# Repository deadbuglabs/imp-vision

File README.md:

# imp-vision

IMP-VISION — Deadbug Labs AI smart glasses: real thermal imaging + night vision, phone-linked. Temple board, firmware, and app.

The glasses connect to a phone and nothing else — no hub, no cloud account, no builder-supplied parts. Complete glasses in the box; the phone app is where the AI experience lives.

## What it sees

Real thermal imaging and real night vision, fused, in glasses you would wear anywhere. Nobody sells that combination. Fused thermal + night-vision systems exist only as military gear — helmet-mounted, bulky, issued rather than bought. IMP-VISION is being built to put both senses in an ordinary frame.

- **Thermal imaging** — a FLIR Lepton-class 160×120 radiometric core on the full-sense build. Real heat signatures, not blobs.
- **Night vision** — a no-IR-cut camera with 940 nm illuminators that emit no visible glow.
- **IR Source Watch** — passive detection of other active IR emitters (camera night-vision arrays, illuminators), labelled with classification and confidence.
- **Camera + microphone** — with a recording LED that is hardwired to the camera: no firmware path can light the camera without lighting the LED.

## Your models, your pick

The app takes any compatible Hugging Face model per role — Eyes, Brain, Ears, Voice — GGUF with mmproj for vision, sized to your phone, license shown before download. Defaults are preselected; the picker is open. Model sets: [Devilishcode/imp-vision-model-sets](https://huggingface.co/Devilishcode/imp-vision-model-sets)

## Status — 2026-11-21

- Temple board (ESP32-S3): routing at 50 unconnected nets, 0 shorts. Not DRC-clean, not fab-ready; a placement respin is the next step.
- Temple firmware v0: compiles clean. The firmware is a dumb pipe — the phone does the thinking.
- Phone app: v0.10.3 — glasses link layer, IR Watch, and a thermal preview surface all working against the phone camera.
- Display variants: in evaluation. The base build is audio-first, no display.

## Design documents

- [app-design.md](app-design.md) — the companion app: voice-first UI, senses, model picker
- [INTEGRATION.md](INTEGRATION.md) — how the temple board, frames, and sensors fit together
- [RING_DESIGN.md](RING_DESIGN.md) — the BLE scroll + click ring
- [INPUT_SOURCES.md](INPUT_SOURCES.md) — ring, mouse, and other input classes
- [PAIR_IMP_PROTOCOL.md](PAIR_IMP_PROTOCOL.md) — how the glasses pair with an IMP-1, and the hard limits on what they may ask it to do
- [SCREEN_CONTROL.md](SCREEN_CONTROL.md) — the display control model for display variants

Deadbug Labs — boards and devices for people who build. https://deadbuglabs.github.io/

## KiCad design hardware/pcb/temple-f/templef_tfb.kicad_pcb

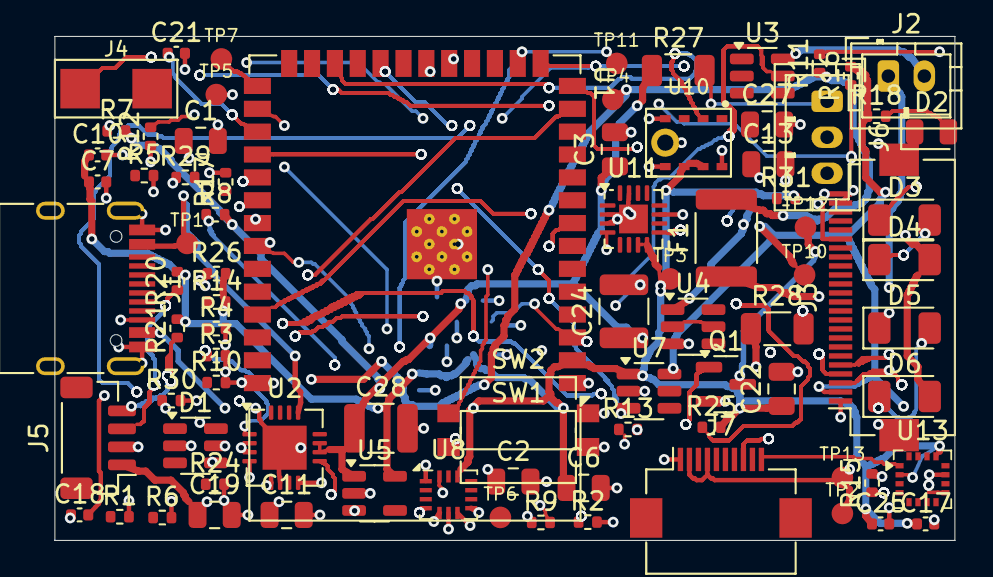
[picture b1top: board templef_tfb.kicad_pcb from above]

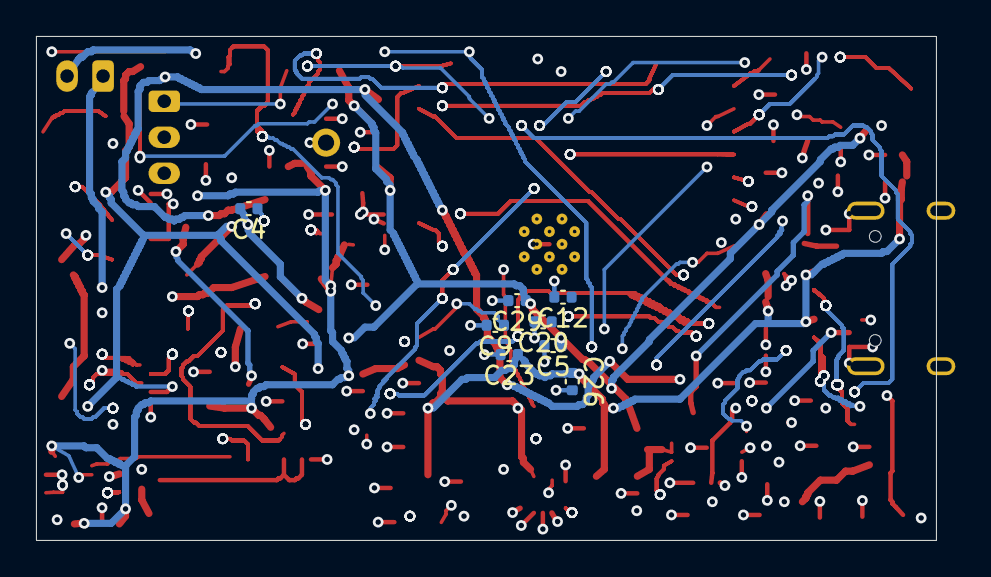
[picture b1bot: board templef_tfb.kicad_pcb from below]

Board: 4 copper layers, 50.0 x 28.0 mm, 91 parts (8 on the bottom side), 70 nets.

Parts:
C1, C2, C3, C6, C11, C13, C19, C22, C27: C_0805_2012Metric
C4, C5, C7, C9, C10, C12, C17, C18, C20, C21, C23, C25, C26, C29: C_0402_1005Metric
C24, C28: C_1210_3225Metric
D1: SOT-23-6
D2: LED_0805_2012Metric
D3, D4, D5, D6: VSMY12940; LED_1206_3216Metric
F1: Fuse_1812_4532Metric
J1: USB_C_Receptacle_HRO_TYPE-C-31-M-12
J2: JST_PH_B2B-PH-K_1x02_P2.00mm_Vertical
J3: Hirose_FH12-24S-0.5SH_1x24-1MP_P0.50mm_Horizontal
J4: J4_Transducer_Lands_2P_P4.0mm
J5: JST_SH_BM04B-SRSS-TB_1x04-1MP_P1.00mm_Vertical
J6: JST_PH_B3B-PH-K_1x03_P2.00mm_Vertical
J7: Hirose_FH12-10S-0.5SH_1x10-1MP_P0.50mm_Horizontal
Q1: SOT-23
R1, R2, R3, R4, R5, R6, R7, R8, R9, R10, R11, R12, R13, R14, R15, R16, R17, R18, R20, R21, R24, R25, R26, R29, R30, R31: R_0402_1005Metric
R27, R28: R_1206_3216Metric
SW1, SW2: SW_Tactile_SPST_NO_Straight_CK_PTS636Sx25SMTRLFS
TP1, TP2, TP3, TP4, TP5, TP6, TP7, TP10, TP11, TP12, TP13: TP_Pad_D1.2mm
U1: ESP32-S3-WROOM-1
U2: QFN-16-1EP_4x4mm_P0.5mm_EP2.45x2.45mm
U3, U4, U7: SOT-23-6
U5: SOT-23-5
U8: Bosch_LGA-14_3x2.5mm_P0.5mm
U10: INMP441_LGA_4.72x3.76
U11: TQFN-16-1EP_3x3mm_P0.5mm_EP1.6x1.6mm
U13: LGA-16_3x3mm_P0.5mm

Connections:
AMP_SD: U1.22, U11.4
BATT_ADC: R11.2, R12.2, U1.15
BAT_CELL: C2.1, F1.2, R9.1, R11.1, TP4.1, U2.2, U2.3
BOOT: R14.1, TP7.1, U1.27
BTN_PHOTO: C21.1, R26.1, SW2.1, U1.29
BTN_PTT: C20.1, R25.1, SW1.1, U1.28
CAM_3V3: C13.1, J3.2, J3.20, R15.2, R16.2, R18.1, TP10.1, U7.6
CAM_CT: C12.1, U7.5
CAM_D0: J3.16, U1.39
CAM_D1: J3.15, U1.38
CAM_D2: J3.14, U1.4
CAM_D3: J3.13, U1.5
CAM_D4: J3.12, U1.6
CAM_D5: J3.11, U1.7
CAM_D6: J3.10, U1.12
CAM_D7: J3.9, U1.17
CAM_HREF: J3.6, U1.9
CAM_PCLK: J3.7, U1.21
CAM_PWDN: J3.18, R17.1
CAM_PWR_EN: U1.30, U7.3
CAM_RESET: J3.17, U1.10
CAM_SIOC: J3.3, R15.1, U1.20
CAM_SIOD: J3.4, R16.1, U1.19
CAM_VSYNC: J3.5, U1.8
CAM_XCLK: J3.8, U1.18
CC1: J1.A5, R1.1
CC2: J1.B5, R2.1
CELL_NEG: C4.2, J2.2, U3.6, U4.1
CELL_POS: F1.1, J2.1
CHG_ILIM: R4.1, U2.12
CHG_ISET: R5.1, U2.16
CHG_PGOOD: R7.1, U1.33, U2.7
CHG_STAT: R8.1, U1.32, U2.9
CHG_TMR: R6.1, U2.14
CHG_TS: R3.1, U2.1
EN: C9.1, R13.1, TP6.1, U1.3
GND: C1.2, C2.2, C3.2, C5.2, C6.2, C7.2, C9.2, C10.2, C11.2, C12.2, C13.2, C17.2, C18.2, C19.2, C20.2, C21.2, C22.2, C23.2, C24.2, C25.2, C26.2, C27.2, C28.2, C29.2, D1.2, D2.1, J1.A1, J1.A12, J1.B1, J1.B12, J1.S1, J3.1, J3.19, J3.23, J3.24, J3.MP, J5.2, J7.1, Q1.2, R1.2, R2.2, R3.2, R4.2, R5.2, R6.2, R10.2, R12.1, R17.2, R24.2, R30.2, SW1.2, SW2.2, TP5.1, U1.1, U1.40, U1.41, U2.4, U2.6, U2.8, U2.17, U4.3, U5.2, U7.2, U8.1, U8.6, U8.7, U10.4, U10.5, U10.6, U10.9, U11.2, U11.3, U11.11, U11.15, U11.17, U13.9, U13.11
I2C_SCL: J5.4, J7.10, R21.1, U1.35, U8.13, U13.1
I2C_SDA: J5.3, J7.9, R20.1, U1.34, U8.14, U13.16
I2S_BCLK: U1.11, U10.1, U11.16
I2S_DIN: R24.1, U1.24, U10.2
I2S_DOUT: U1.25, U11.1
I2S_WS: U1.23, U10.3, U11.14
ILL_A1: D3.1, J6.1, R27.2
ILL_A2: D5.1, J6.2, R28.2
ILL_G: Q1.1, R29.2, R30.1
ILL_K: D4.2, D6.2, J6.3, Q1.3, TP12.1
ILL_M1: D3.2, D4.1
ILL_M2: D5.2, D6.1
IMU_INT: TP11.1, U1.16, U8.4
IR_ILLUM_EN: R29.1, U1.31
LEP_CS: J7.8, R31.1, U1.37
LEP_MISO: J7.6, U1.26
LEP_SCK: J7.7, U1.36
MAG_CAP: C27.1, U13.10
PROT_CS: R10.1, U3.2
PROT_DMID: U4.2, U4.5
PROT_OC: U3.3, U4.4
PROT_OD: U3.1, U4.6
PROT_VDD_F: C4.1, R9.2, U3.5
REC_LED_A: D2.2, R18.2
SPK_N: J4.2, U11.10
SPK_P: J4.1, U11.9
SYS: C3.1, C5.1, C24.1, C28.1, C29.1, J7.2, J7.4, R7.2, R8.2, R27.1, R28.1, TP2.1, TP13.1, U2.10, U2.11, U5.1, U5.3
USB_DN: D1.4, U1.13
USB_DN_C: D1.3, J1.A7, J1.B7
USB_DP: D1.6, U1.14
USB_DP_C: D1.1, J1.A6, J1.B6
V3_3: C6.1, C7.1, C10.1, C11.1, C17.1, C18.1, C19.1, C22.1, C23.1, C25.1, C26.1, J5.1, R13.2, R14.2, R20.2, R21.2, R25.2, R26.2, R31.2, TP3.1, U1.2, U5.5, U7.1, U8.5, U8.8, U8.12, U10.7, U10.8, U11.7, U11.8, U13.2, U13.4, U13.13
VBUS_5V: C1.1, D1.5, J1.A4, J1.A9, J1.B4, J1.B9, TP1.1, U2.5, U2.13
